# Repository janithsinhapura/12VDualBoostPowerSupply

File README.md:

# 12V Dual Boost Converter Power Supply Hardware design 

This repository contains the Kicad PCB design files for 12V Dual Boost Converter Based on XL6009,

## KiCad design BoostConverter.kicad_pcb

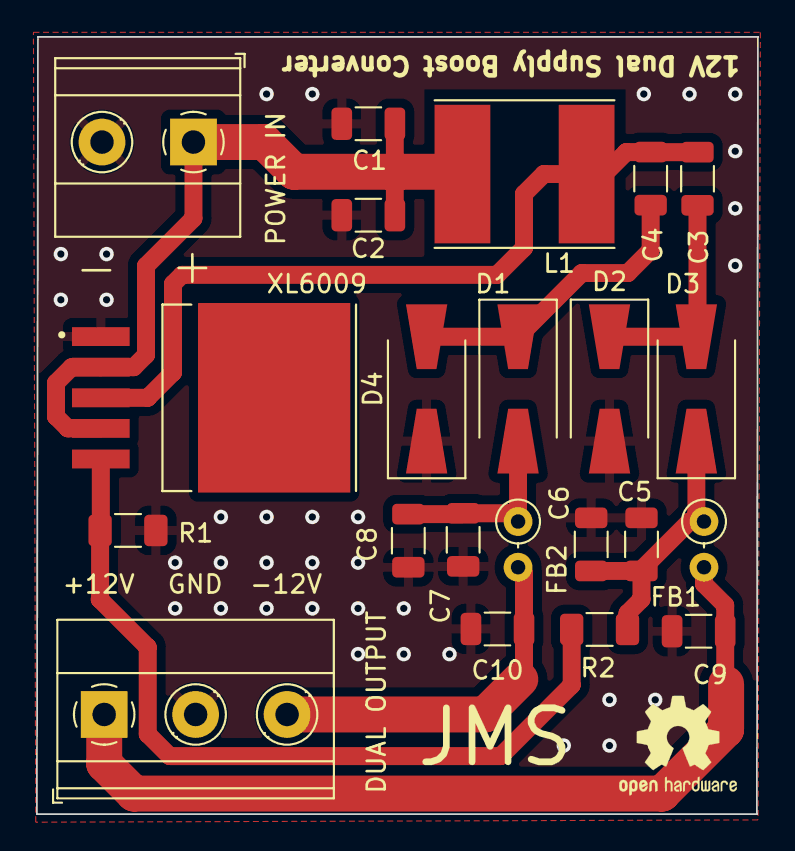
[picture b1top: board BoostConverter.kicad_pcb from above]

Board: 2 copper layers, 40.1 x 43.2 mm, 22 parts (0 on the bottom side), 10 nets.

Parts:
C1, C2, C3, C4, C5, C6, C7, C8, C9, C10: 10uF; C_1206_3216Metric
D1, D2, D3, D4: SS34; D_SMA-SMB_Universal_Handsoldering
DUAL OUTPUT : Output; TerminalBlock_Phoenix_MKDS-1,5-3-5.08_1x03_P5.08mm_Horizont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
FB1, FB2: FerriteBead; L_Axial_L5.3mm_D2.2mm_P2.54mm_Vertical_Vishay_IM-1
L1: 20uH; L_Taiyo-Yuden_NR-80xx_HandSoldering
POWER IN: Input; TerminalBlock_Phoenix_MKDS-1,5-2-5.08_1x02_P5.08mm_Horizont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
R1, R2: R; R_1206_3216Metric_Pad1.30x1.75mm_HandSolder
XL6009: XL6009

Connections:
GND: C1.2, C2.2, C5.2, C6.2, C7.1, C8.1, C9.2, C10.1, D3.2 (A), D4.1 (K), DUAL OUTPUT.2, POWER IN.2, R1.1, XL6009.1 (GND)
unnamed: C7.2, C8.2, D1.2 (A), FB2.1
unnamed: C4.2, D1.1 (K), D4.2 (A)
unnamed: C3.2, D2.2 (A), D3.1 (K)
unnamed: C5.1, C6.1, D2.1 (K), FB1.1, R2.2
unnamed: C9.1, DUAL OUTPUT.1, FB1.2
unnamed: C10.2, DUAL OUTPUT.3, FB2.2
unnamed: C1.1, C2.1, L1.1, POWER IN.1, XL6009.2 (EN), XL6009.4 (VIN)
unnamed: R1.2, R2.1, XL6009.5 (FB)
unnamed: C3.1, C4.1, L1.2, XL6009.3 (SW)

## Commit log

2023-12-13 Added Version 0.1 Project Files
2023-12-13 Added pcb 3d view file
